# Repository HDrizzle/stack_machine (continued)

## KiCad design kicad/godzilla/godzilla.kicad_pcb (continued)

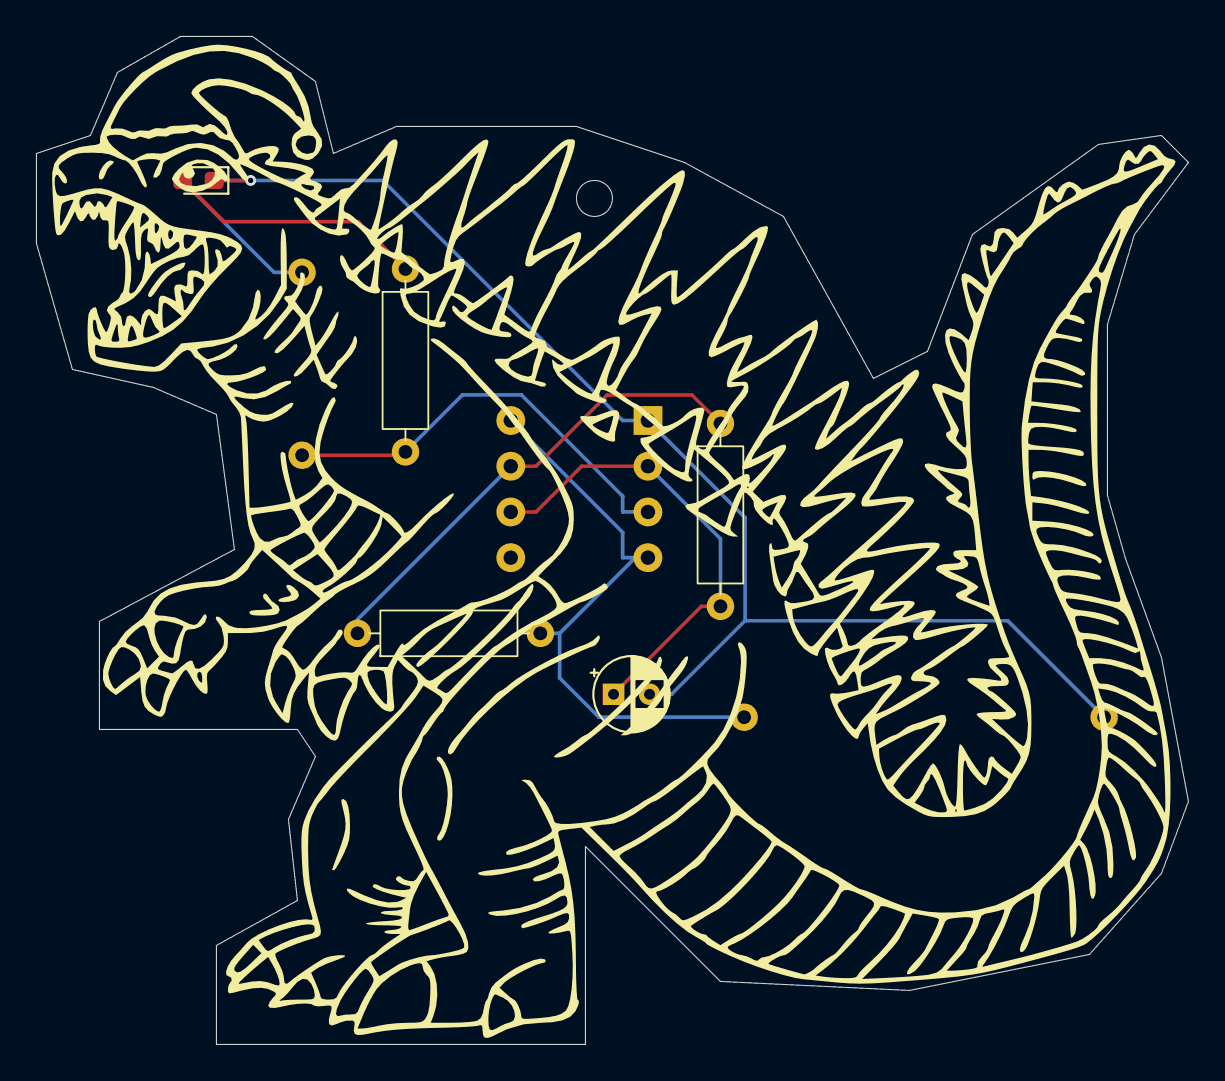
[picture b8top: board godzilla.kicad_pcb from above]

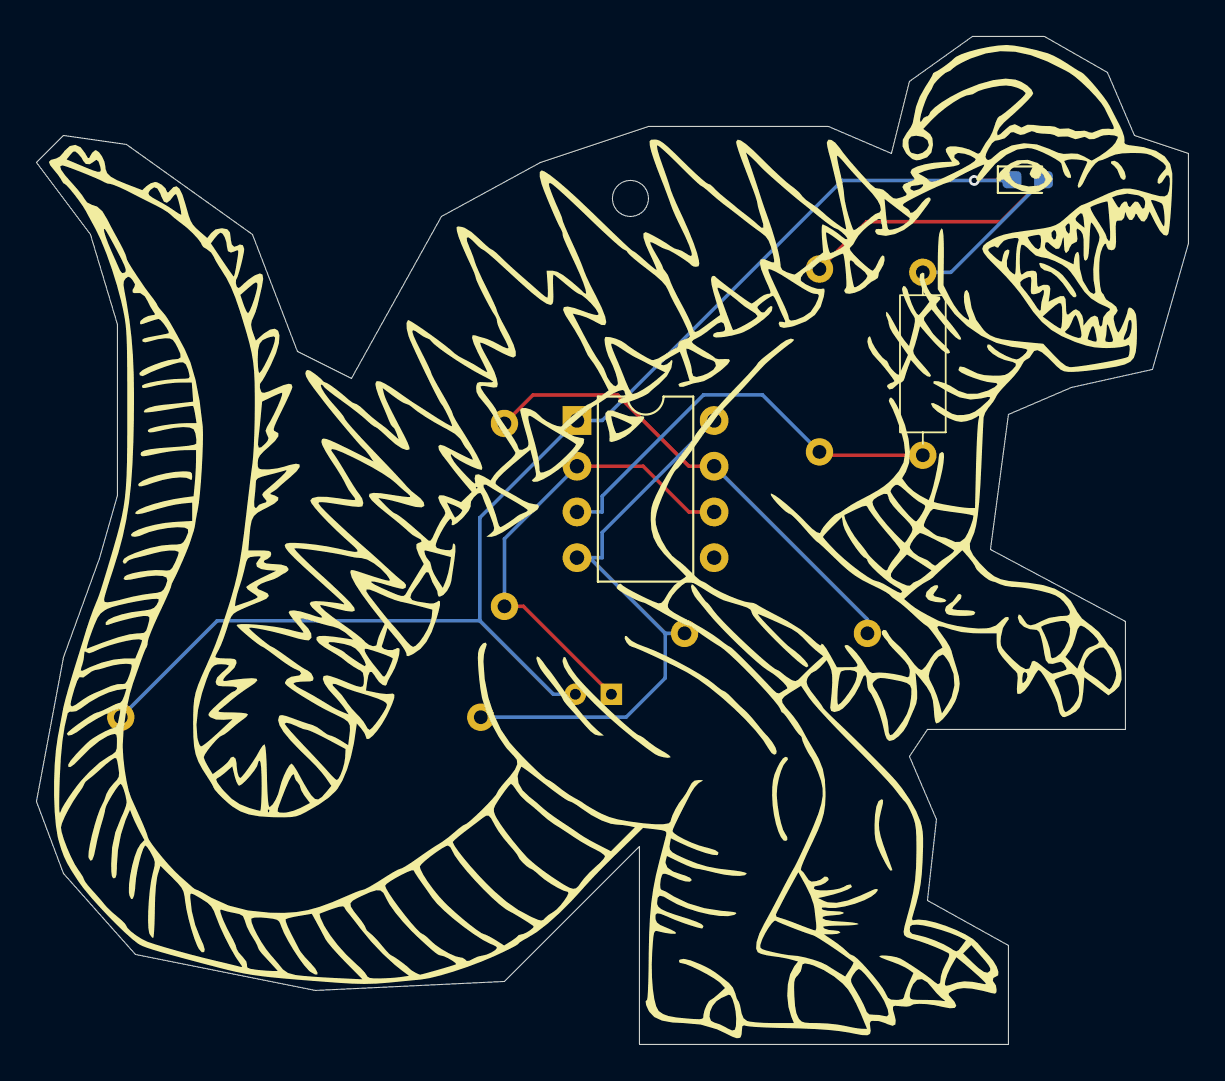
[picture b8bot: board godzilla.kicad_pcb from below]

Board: 2 copper layers, 64.0 x 56.0 mm, 10 parts (3 on the bottom side), 7 nets.

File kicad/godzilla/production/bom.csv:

Designator,Footprint,Quantity,Value,LCSC Part #
BT1,battery_holder_coin,1,Battery_Cell,
C1,CP_Radial_D4.0mm_P2.00mm,1,C,
"D1, D2",0603,2,LED,
"R1, R2, R3, R4",0.4_pitch_resistor,4,R,
U1,DIP-8_W7.62mm,1,NE555P,

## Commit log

2024-03-11 Copied and updated some things from g-docs
2024-03-11 Some fixes
2024-03-13 Got rid of arbitrary-sized objects
2024-03-13 Added some graphics
2024-03-15 Improved stack controller
2024-03-16 More documentation
2024-03-17 Assembly examples and GPIO
2024-03-17 Added rust stuff
2024-03-19 Working on emulator
2024-04-04 Clarified some details and swapped PUSH instruction with WRITE
2024-04-05 Got fibonacci program working
2024-04-24 Bus timing drawing
2024-05-07 Updated README with call stack and stack frames
2024-05-08 Details
2024-05-14 Fixed emulator and examples
2024-05-16 Indep study got rejected
2024-05-23 Started using KiCad
2024-05-25 CAD stuff
2024-05-26 I love KiCad
2024-05-29 timing stuff and CAD
2024-05-31 Improved timing
2024-06-01 Possibly final design of stack controller
2024-06-05 kicad stuff and timing
2024-06-07 Finished schematic for motherboard
2024-06-11 Work on control unit
2024-06-12 Work on call stack and instruction sequence timing
2024-06-13 Completed design for call stack
2024-06-13 Finished logic for control unit
2024-06-17 Messing w/ simulation & updating emulator
2024-06-21 stuff
2024-06-24 Finished main PCB design
2024-06-29 Working on clock
2024-07-03 Designed sample board
2024-07-03 Fixed rust error
2024-07-11 Increased clock PCB clearances
2024-07-12 Added pulldown resistors to clock module inputs
2024-07-22 Working on control unit schematic
2024-07-22 Finished central timing schematic & created progress table
2024-07-23 Finished startup controller
2024-07-26 Working on ALU
2024-07-26 Done w/ ALU schematic
2024-07-26 Updating parts spreadsheet (not done)
2024-07-30 Working on GPRAM in CV and timing diagrams (not done yet)
2024-08-02 Finished GPRAM in CV
2024-08-02 Started GPRAM schematic
2024-08-03 Added pullup resistors to control unit memory address
2024-08-04 Working on GPRAM schematic
2024-08-05 Finished IO controller schematic
2024-08-10 Verified GPRAM schematic
2024-08-10 Finished GPRAM PCB
2024-08-11 Finished central timing PCB
2024-08-11 Finished call stack schematic
2024-08-13 Finished prog memory timing diagrams
2024-08-19 Finished some more PCBs and uploaded to JLCPCB
2024-08-20 Almost done with prog mem schematic
2024-08-20 Finished prog mem schematic
2024-08-20 Finished last PCB
2024-08-24 Updating emulator
2024-09-13 Added github pages config
2024-09-21 Bus addressing patch
2024-10-13 Lots of stuff
2024-10-16 Added photo of it partialy completed
2024-10-16 Working on program upload
2024-11-18 Working on compiler
2024-11-20 It be compiling
2024-11-22 u5i7tynmfuhejg
2024-11-23 The (limited) tests pass
2024-11-26 Mostly working
2024-12-12 Added compiler functionality to deal with stack offset
2024-12-12 Fixed broken test
2024-12-14 Led matrix progress
2024-12-16 Sick new LED block footprints
2024-12-22 Almost done with led matrix schematic
2024-12-22 Schematic probably done
2024-12-23 LED matrix PCB done
2024-12-23 Fixed prog mem and updated PCB
2024-12-23 Fixed clock board
2024-12-29 Screen emulator working
2024-12-29 Working on tetris program
2024-12-31 Added failsafe to LED matrix and some other stuff
2024-12-31 Added connector on IO controller to support display
2025-01-01 Improved readme
2025-01-02 Fixed led matrix board
2025-01-03 Fixed led matrix controller
2025-01-07 Added new led matrix board for the 8x8 displays
2025-01-09 Tetris program draw-shape and init-next-shape-from-storage functions work
2025-01-09 Tetris shape rotating
2025-01-16 Got read-input working
2025-01-17 Debug movement
2025-01-18 Tetris progress
2025-01-19 Tetris line deleting
2025-01-19 Tetris almost working
2025-01-20 Tetris worksgit add .git add .git add .
2025-01-20 TETRIS WORKS
2025-01-26 Added new shape to tetris and fixed minor bug
2025-02-08 Brushless controller
2025-02-19 Point test and work on optimizing tetris
2025-02-20 Optimized tetris 7 MHz -> 1 MHz
2025-03-02 Display name
2025-03-08 Pong progress
2025-03-09 Now to debug pong
2025-03-09 Pong finished
2025-03-12 Tetris for faulty stack
2025-03-29 Control panel almost done
2025-04-04 Improved control panel and fixed music program
2025-04-05 Finished control panel
2025-04-11 before using copilot
2025-04-16 Motion canvas project created
2025-04-22 Motion canvas progress
2025-04-26 Presentation progress
2025-05-03 Almost done on memory fade
2025-05-10 Logic simulation in presentation
2025-05-11 Working on logic sim
2025-05-11 More gates
2025-05-13 Broke it but for the better
2025-05-15 Less broken
2025-05-15 Working, now to make circuits nest-able
2025-05-17 Logic sim works
2025-05-18 Improved gates demo
2025-05-20 More animations comming
2025-05-21 Circuit replacement animation works
2025-05-21 Working on 8 bit latch
2025-05-24 Form part of larger circuit animation almost working
2025-05-24 Fixed larger circuit animation and making slides
2025-05-25 Progress
2025-05-26 Actually working on slides now
2025-05-29 Presentation as done as its gonna get
2025-06-26 Got tetris running @ 1.5 MHz
2025-09-07 Working on vector graphics specs
2025-09-22 Nyan cat
2025-10-02 Finished vector timing
2025-10-21 Vector timing changed
2025-11-05 Vector controller memory reader works
2025-11-25 Vector controller finally i think complete
2025-12-05 Working on vector controller
2025-12-08 Fixed vector timing for stupid DACs
2025-12-25 Progress on vectors
2025-12-25 KiCad progress
2025-12-27 Progress on vector thingy
2025-12-27 Potentially finished kicad
2025-12-27 Satisfied ERC
2026-01-06 About to change bus loading
2026-01-07 Bus loading fixed
2026-01-08 Vector thingy almost completely verified except math and DAC stuff
2026-01-10 Vector graphics board finished
2026-01-15 Moved rusty logic circuits into this repo
2026-01-23 Added V2 into this repo
2026-01-24 Work on sequencer in rusty logic
2026-01-26 Sequencer possible finished in rusty logic
2026-01-26 Finished bus controller in rusty logic
2026-01-27 Progress in rusty logic
2026-01-28 GPRAM in rusty logic
2026-01-29 GPRAM sequencer in rusty logic verified
2026-01-30 Stack sequencer almost done in rusty logic
2026-01-30 Stack and gpram manager done
2026-01-30 Coming together
2026-01-31 Improved bus timing
2026-02-02 Got delayed instruction loading reliable
2026-02-03 fixed bus rx extend and started ALU
2026-02-03 ALU in rusty logic
2026-02-04 Fixed instruction read ready timing
2026-02-05 Wiring it together
2026-02-07 Started defining timers and interrupts
2026-02-08 Finished interrupt handler and started timers
2026-02-10 Rusty logic progress
2026-02-11 Gotta update the assembler for new hardware version
2026-02-12 Fibonacci achieved
2026-02-17 Added photo
2026-02-25 Save files should work
2026-02-27 Rusty logic modifications
2026-03-01 Fixing timing issues
2026-03-02 Tetris in progress
2026-03-03 About to fix same device TX and RX problem
2026-03-03 Probably fixed same device tx rx problem
2026-03-04 Tetris draw shapes first time
2026-03-10 Assembler now supports version 2
2026-03-15 Fixed interrupts and work on emulator for v2
2026-03-15 Timers working
2026-03-16 V2 progress table
2026-03-18 Testing gpram instruction loading
2026-03-20 GPRAM sharing works
2026-03-20 Physical construction planning
2026-03-23 Finally using kicad
2026-03-23 Sequencer almost checked
2026-03-23 2 circuits verified
2026-03-24 Prog mem verified
2026-03-25 Debug figured out and work on ctrl unit main
2026-03-25 Control unit main schematic verified
2026-03-26 Bus sequencer kicad verified
2026-03-28 Work mostly on bus
2026-03-30 Work on bus
2026-03-30 Bus and starter verified
2026-04-09 ALU v2 verified
2026-04-09 Stack data v2 verified
